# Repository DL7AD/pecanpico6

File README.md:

# Pecan Pico 6 - Pico solar powered APRS tracker

This are the EGALE CAD files for the Pecan Pico 6 project. Pecan Pico is a very small solar powered balloon APRS tracker
in the size of an AAA battery cell. It's powered by a LiFePO4 battery which can be charged by solar cells.

The PCB itself has all the power management features (charging and discharging) integrated, so it needs no external
power supply. It has:
- GPS receiver (ublox MAX7/8)
- NXP LPC1114 microcontroller
- Si4063 transmitter (for APRS transmission)
- Bosch BMP180 (for measure temperature and airpressure)

With the recommended LiFePO4 (200mAh AAA) battery cell, the tracker has a weight of just 13g. It's main
purpose is high altitude ballooning. This particular tracker has been made for super pressure balloons which can fly
for weeks. The solar powered PCB can almost stay alive forever.

The source code for the NXP LPC1114 on the board can be found here: https://www.github.com/DL7AD/pecan-lpc11xx

Author: sven.steudte@gmail.com

https://kt5tk.files.wordpress.com/2015/08/dscn7470.jpg

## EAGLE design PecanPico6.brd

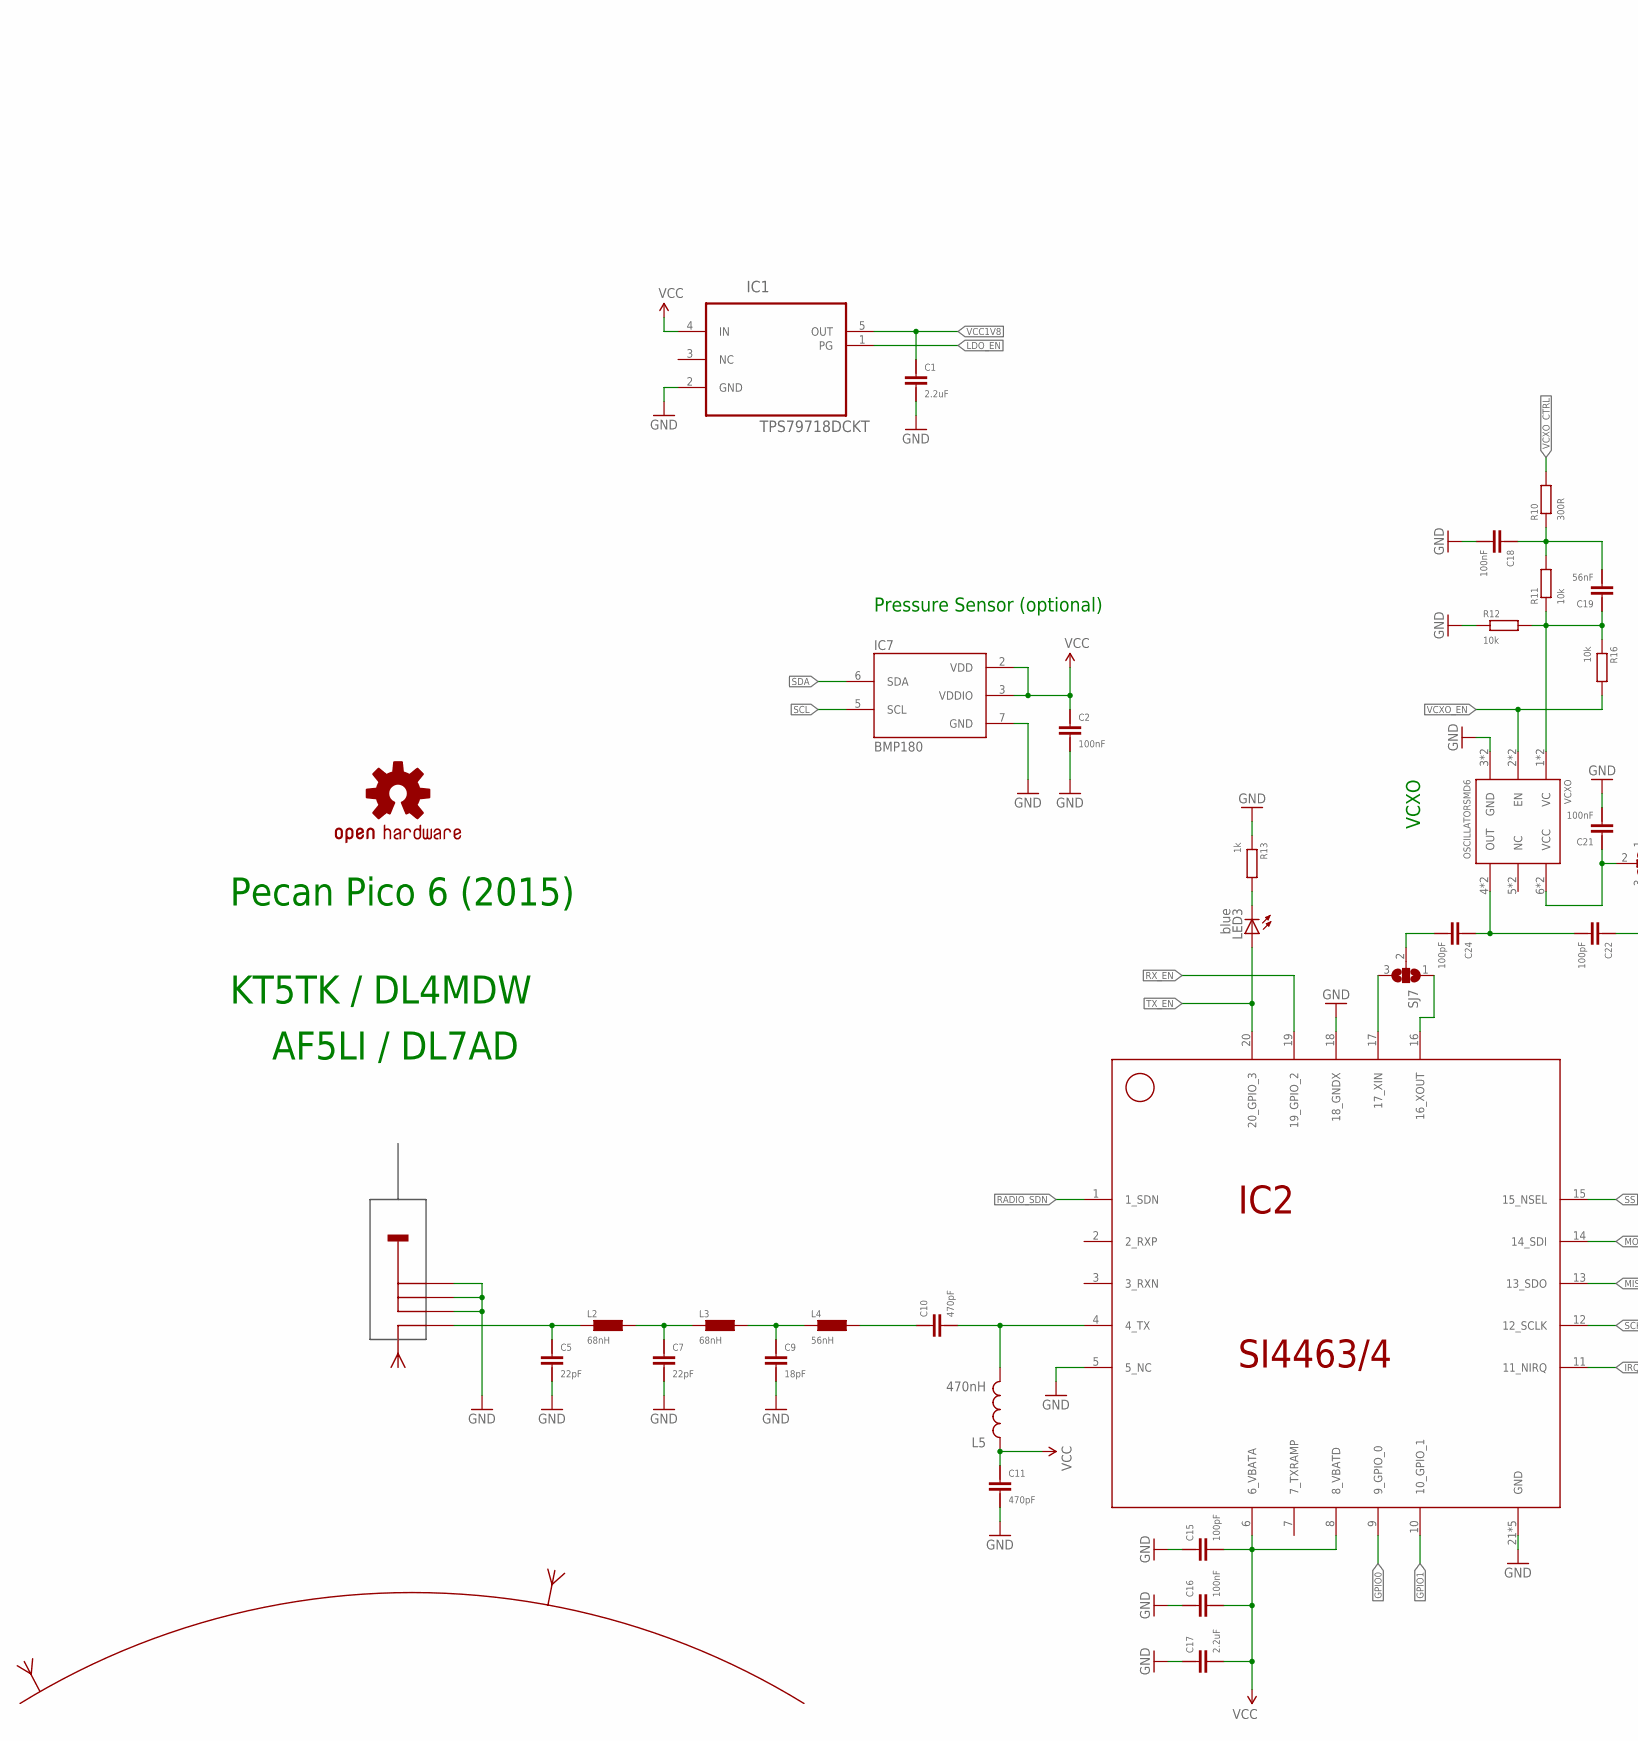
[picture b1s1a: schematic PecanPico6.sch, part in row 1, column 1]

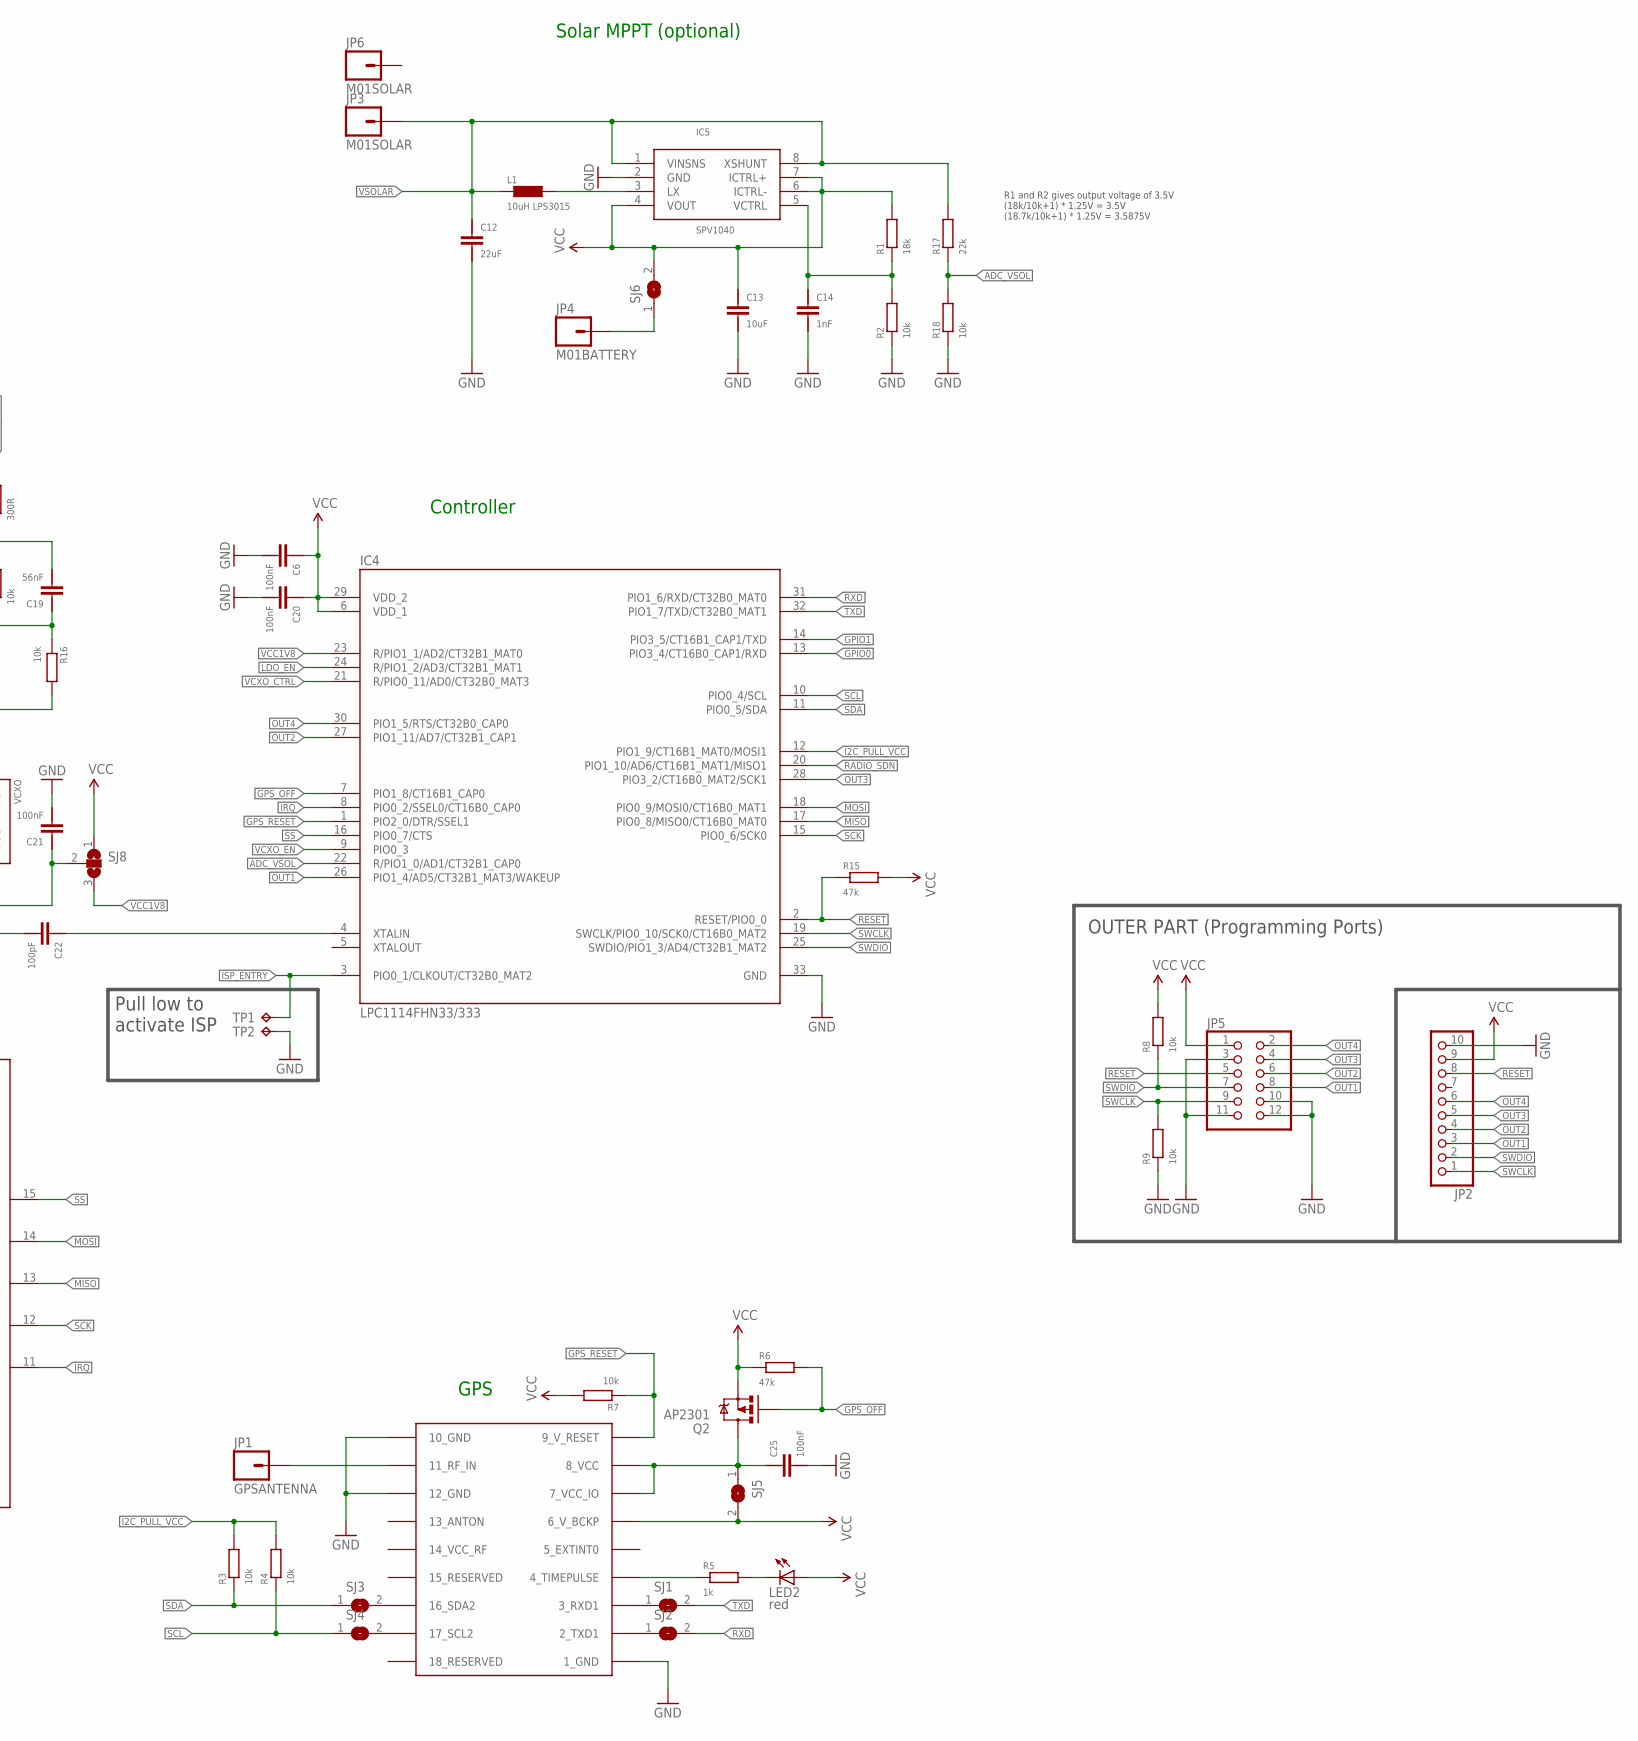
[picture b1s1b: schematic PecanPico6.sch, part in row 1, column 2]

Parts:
C1, C17: 2.2uF; 0603; MPN 225CKH250M
C2, C6, C16, C18, C20, C21, C25: 100nF; 0402
C5, C7: 22pF; 0402
C9: 18pF; 0402
C10, C11: 470pF; 0402
C12: 22uF; 0805
C13: 10uF; 0805
C14: 1nF; 0402
C15, C22, C24: 100pF; 0402
C19: 56nF; 0402
IC1: TPS79718DCKT; SOT65P210X110-5N
IC2: SI4463/4; QFN-20
IC3: UBLOX_MAX-6
IC4: LPC1114FHN33/333; QFN65P700X700X100-33N
IC5: SPV1040; TSSOP8
IC7: BMP180
JP1: GPSANTENNA; PAD2_1.8X0.9
JP2: PINHD-1X10; 1_27X3_PINHEAD_1X10S
JP3, JP6: M01SOLAR; PAD2_1.8X0.9
JP4: M01BATTERY; PAD3.5X7.0
JP5: PINHD-2X6; 2X06
L1: 10uH LPS3015; LPS3015
L2, L3: 68nH; 0402
L4: 56nH; 0402
L5: 470nH; 0805
LED2: red; LED-0603
LED3: blue; LED-0603
LOGO1: OSHW-LOGOS; OSHW-LOGO-S
Q2: AP2301; SOT23-3
R1: 18k; 0402
R2, R3, R4, R7, R8, R9, R11, R12, R16, R18: 10k; 0402
R5, R13: 1k; 0402
R6, R15: 47k; 0402
R10: 300R; 0402
R17: 22k; 0402
SJ1, SJ2, SJ3, SJ4, SJ5, SJ6: SJ
SJ7, SJ8: SJ2W; SJ_2
TP1, TP2: TPTP07R; TP07R
U$1: ANTENNAPAD
VCXO: OSCILLATORSMD6; CRYSTAL-SMD-7.5X5.2-6PIN

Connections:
ADC_VSOL: IC4.22 (R/PIO1_0/AD1/CT32B1_CAP0), R17.P$1 (1), R18.P$2 (2)
GPIO0: IC2.9 (9_GPIO_0), IC4.13 (PIO3_4/CT16B0_CAP1/RXD)
GPIO1: IC2.10 (10_GPIO_1), IC4.14 (PIO3_5/CT16B1_CAP1/TXD)
GPS_OFF: IC4.7 (PIO1_8/CT16B1_CAP0), Q2.1 (G), R6.P$2 (2)
GPS_RESET: IC3.9_V_RESET, IC4.1 (PIO2_0/DTR/SSEL1), R7.P$1 (1)
I2C_PULL_VCC: IC4.12 (PIO1_9/CT16B1_MAT0/MOSI1), R3.P$2 (2), R4.P$2 (2)
IRQ: IC2.11 (11_NIRQ), IC4.8 (PIO0_2/SSEL0/CT16B0_CAP0)
ISP_ENTRY: IC4.3 (PIO0_1/CLKOUT/CT32B0_MAT2), TP1.TP
LDO_EN: IC1.1 (PG), IC4.24 (R/PIO1_2/AD3/CT32B1_MAT1)
MISO: IC2.13 (13_SDO), IC4.17 (PIO0_8/MISO0/CT16B0_MAT0)
MOD1: C18.P$2 (2), C19.P$1 (1), R10.P$1 (1), R11.P$2 (2)
MOSI: IC2.14 (14_SDI), IC4.18 (PIO0_9/MOSI0/CT16B0_MAT1)
unnamed: C7.P$2 (2), L2.P$2 (2), L3.P$1 (1)
unnamed: C24.P$1 (1), SJ7.2
unnamed: IC3.11_RF_IN, JP1.1
unnamed: C22.P$2 (2), IC4.4 (XTALIN)
unnamed: LED2.C, R5.P$2 (2)
unnamed: JP4.1, SJ6.1
unnamed: IC3.4_TIMEPULSE, R5.P$1 (1)
unnamed: LED3.C, R13.P$2 (2)
unnamed: IC2.17 (17_XIN), SJ7.3
unnamed: C25.P$2 (2), IC3.7_VCC_IO, IC3.8_VCC, Q2.3 (D), SJ5.1
unnamed: C22.P$1 (1), C24.P$2 (2), VCXO.4 (OUT), VCXO.4INNER (OUT)
unnamed: C21.P$2 (2), SJ8.2, VCXO.6 (VCC), VCXO.6INNER (VCC)
unnamed: IC3.3_RXD1, SJ1.1
unnamed: IC2.16 (16_XOUT), SJ7.1
unnamed: IC3.2_TXD1, SJ2.1
unnamed: C19.P$2 (2), R11.P$1 (1), R12.P$2 (2), R16.P$1 (1), VCXO.1 (VC), VCXO.1INNER (VC)
unnamed: C10.P$1 (1), IC2.4 (4_TX), L5.2
unnamed: IC3.16_SDA2, SJ3.2
unnamed: IC3.17_SCL2, SJ4.2
unnamed: C10.P$2 (2), L4.P$2 (2)
unnamed: IC5.3 (LX), L1.2_1 (2), L1.2_2 (2), L1.2_3 (2), L1.2_4 (2), L1.2_5 (2), L1.2_6 (2), L1.2_7 (2), L1.2_8 (2), L1.2_9 (2)
unnamed: C9.P$2 (2), L3.P$2 (2), L4.P$1 (1)
unnamed: C5.P$2 (2), L2.P$1 (1), U$1.ANT
unnamed: C14.P$2 (2), IC5.5 (VCTRL), R1.P$1 (1), R2.P$2 (2)
unnamed: C1.P$1 (1), C2.P$1 (1), C5.P$1 (1), C6.P$1 (1), C7.P$1 (1), C9.P$1 (1), C11.P$1 (1), C12.P$1 (1), C13.P$1 (1), C14.P$1 (1), C15.P$2 (2), C16.P$2 (2), C17.P$2 (2), C18.P$1 (1), C20.P$1 (1), C21.P$1 (1), C25.P$1 (1), IC1.2 (GND), IC2.5 (5_NC), IC2.18 (18_GNDX), IC2.21 (GND), IC2.22 (GND), IC2.23 (GND), IC2.24 (GND), IC2.25 (GND), IC3.1_GND, IC3.10_GND, IC3.12_GND, IC4.33 (GND), IC5.2 (GND), IC7.7 (GND), JP2.10, JP5.3, JP5.10, JP5.11, JP5.12, R2.P$1 (1), R9.P$1 (1), R12.P$1 (1), R13.P$1 (1), R18.P$1 (1), TP2.TP, U$1.GND1, U$1.GND2, U$1.GND3, VCXO.3 (GND), VCXO.3INNER (GND)
OUT1: IC4.26 (PIO1_4/AD5/CT32B1_MAT3/WAKEUP), JP2.3, JP5.8
OUT2: IC4.27 (PIO1_11/AD7/CT32B1_CAP1), JP2.4, JP5.6
OUT3: IC4.28 (PIO3_2/CT16B0_MAT2/SCK1), JP2.5, JP5.4
OUT4: IC4.30 (PIO1_5/RTS/CT32B0_CAP0), JP2.6, JP5.2
RADIO_SDN: IC2.1 (1_SDN), IC4.20 (PIO1_10/AD6/CT16B1_MAT1/MISO1)
RESET: IC4.2 (RESET/PIO0_0), JP2.8, JP5.5, R15.P$1 (1)
RXD: IC4.31 (PIO1_6/RXD/CT32B0_MAT0), SJ2.2
RX_EN: IC2.19 (19_GPIO_2)
SCK: IC2.12 (12_SCLK), IC4.15 (PIO0_6/SCK0)
SCL: IC4.10 (PIO0_4/SCL), IC7.5 (SCL), R4.P$1 (1), SJ4.1
SDA: IC4.11 (PIO0_5/SDA), IC7.6 (SDA), R3.P$1 (1), SJ3.1
SS: IC2.15 (15_NSEL), IC4.16 (PIO0_7/CTS)
SWCLK: IC4.19 (SWCLK/PIO0_10/SCK0/CT16B0_MAT2), JP2.1, JP5.9, R9.P$2 (2)
SWDIO: IC4.25 (SWDIO/PIO1_3/AD4/CT32B1_MAT2), JP2.2, JP5.7, R8.P$1 (1)
TXD: IC4.32 (PIO1_7/TXD/CT32B0_MAT1), SJ1.2
TX_EN: IC2.20 (20_GPIO_3), LED3.A
VCC1V8: C1.P$2 (2), IC1.5 (OUT), IC4.23 (R/PIO1_1/AD2/CT32B1_MAT0), SJ8.3
VCC15: C2.P$2 (2), C6.P$2 (2), C11.P$2 (2), C13.P$2 (2), C15.P$1 (1), C16.P$1 (1), C17.P$1 (1), C20.P$2 (2), IC1.4 (IN), IC2.6 (6_VBATA), IC2.8 (8_VBATD), IC3.6_V_BCKP, IC4.6 (VDD_1), IC4.29 (VDD_2), IC5.4 (VOUT), IC5.6 (ICTRL-), IC5.7 (ICTRL+), IC7.2 (VDD), IC7.3 (VDDIO), JP2.9, JP5.1, L5.1, LED2.A, Q2.2 (S), R1.P$2 (2), R6.P$1 (1), R7.P$2 (2), R8.P$2 (2), R15.P$2 (2), SJ5.2, SJ6.2, SJ8.1
VCXO_CTRL: IC4.21 (R/PIO0_11/AD0/CT32B0_MAT3), R10.P$2 (2)
VCXO_EN: IC4.9 (PIO0_3), R16.P$2 (2), VCXO.2 (EN), VCXO.2INNER (EN)
VSOLAR: C12.P$2 (2), IC5.1 (VINSNS), IC5.8 (XSHUNT), JP3.1, L1.1_1 (1), L1.1_2 (1), L1.1_3 (1), L1.1_4 (1), L1.1_5 (1), L1.1_6 (1), L1.1_7 (1), L1.1_8 (1), L1.1_9 (1), R17.P$2 (2)

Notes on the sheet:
KT5TK / DL4MDW
Controller
GPS
VCXO
Pressure Sensor (optional)
Pecan Pico 6 (2015)
Solar MPPT (optional)
AF5LI / DL7AD
OUTER PART (Programming Ports)
Pull low to
activate ISP
R1 and R2 gives output voltage of 3.5V (18k/10k+1) * 1.25V = 3.5V (18.7k/10k+1) * 1.25V = 3.5875V

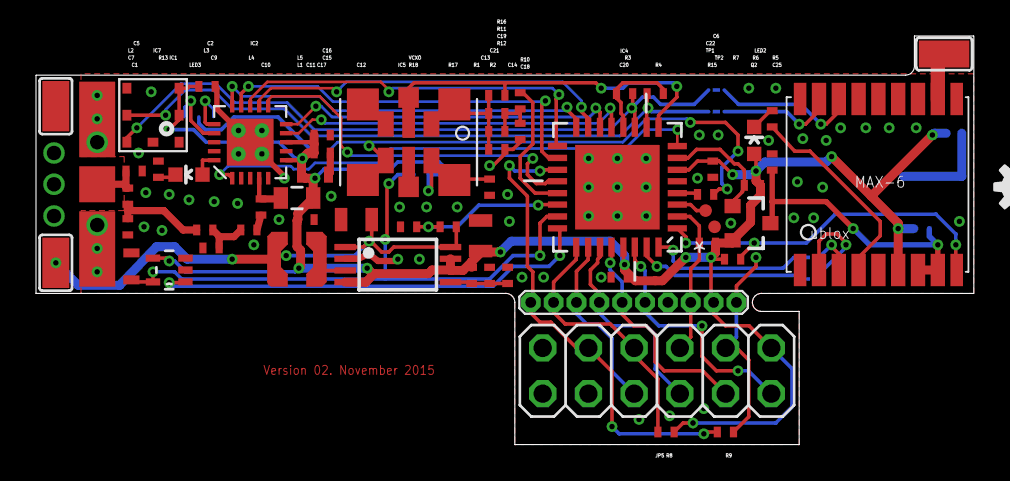
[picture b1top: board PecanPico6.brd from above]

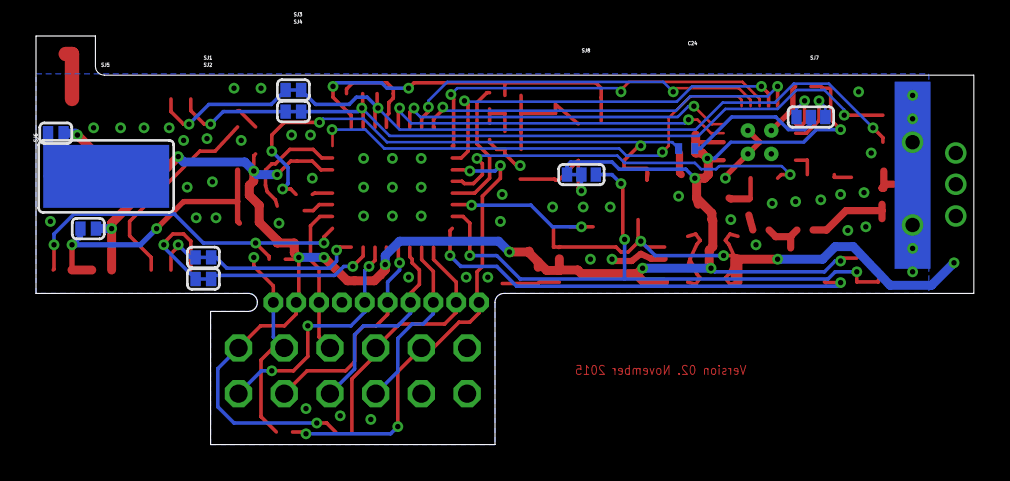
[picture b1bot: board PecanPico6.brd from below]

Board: 2 copper layers, 52.1 x 22.7 mm, 71 parts (10 on the bottom side), 57 nets.

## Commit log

2015-03-17 Changed net class restrictions, fixed DRC errors on board
2015-03-17 Corrected 'UART TXD,RXD switched' error
2015-03-18 Moved misplaced IC label
2015-03-18 Added hackvana gerber files
2015-03-30 Added interrupt signal,option between XIN and XOUT
2015-03-30 mproved SDA SCL signal routing
2015-04-03 Added version date
2015-04-03 Changed version date to copper layer
2015-04-06 Moved some components to make it look better
2015-04-06 Recreated GERBERs
2015-04-24 Added image export files
2015-07-11 Initial commit of new PecanPico6b degin
2015-07-11 Removed old brd and sch images
2015-07-11 Moved microcontroller
2015-07-12 Sorted parts
2015-07-12 Done some more sorting
2015-07-13 Moved stuff around the PCB
2015-07-16 Added programmer jumpers
2015-07-28 Moved stuff around on the board
2015-11-02 Created version 6b Removed RX part Removed UART pinheader below GPS module Enlarged Solar pad Fixed VCC_IO pin connection at GPS Enlarged Board for holes
2015-11-02 Moved solar pads
2015-11-02 Fixed DRC errors
2015-11-02 Updated gerber files

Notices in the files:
parts and their libraries:
SparkFun-FreqCtrl_TK: Licensing: CC v3.0 Share-Alike You are welcome to use this library for commercial purposes.
SparkFun-DiscreteSemi: Licensing: Creative Commons ShareAlike 4.0 International - https://creativecommons.org/licenses/by-sa/4.0
